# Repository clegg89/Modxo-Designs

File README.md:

# Modxo Designs
A set of custom [Modxo](https://github.com/Team-Resurgent/modxo) boards.

All boards have 128Mb (16MB) of flash and use a custom board variant.

## Comparison

| Feature | Micro | Mini | Mega |
| ------- | ----- | ---- | ---- |
| 128Mb (16MB) of flash | ✅ | ✅ | ✅ |
| On-board RGB LED | ✅ | ✅ | ✅ |
| USB port for DFU Update | ✅ | ✅ | ✅ |
| D0 Port/Solder Pad | ✅ | ✅ | ✅ |
| Xbox I2C Port | ❌ | ✅ | ✅ |
| LCD Support | ❌ | ✅ | ✅ |
| RGB Output Port | ❌ | ✅ | ✅ |
| Expansion I2C Port | ❌ | ✅ | ✅ |
| RP2350 MCU | ❌ | ❌ | ✅ |
| UART Port | ❌ | ❌ | ✅ |
| Micro SD Card Slot | ❌ | ❌ | ✅ |
| Debug Support | ❌ | ❌ | ✅ |
| R3MUX (X3) Support | ❌ | ❌ | ✅ |

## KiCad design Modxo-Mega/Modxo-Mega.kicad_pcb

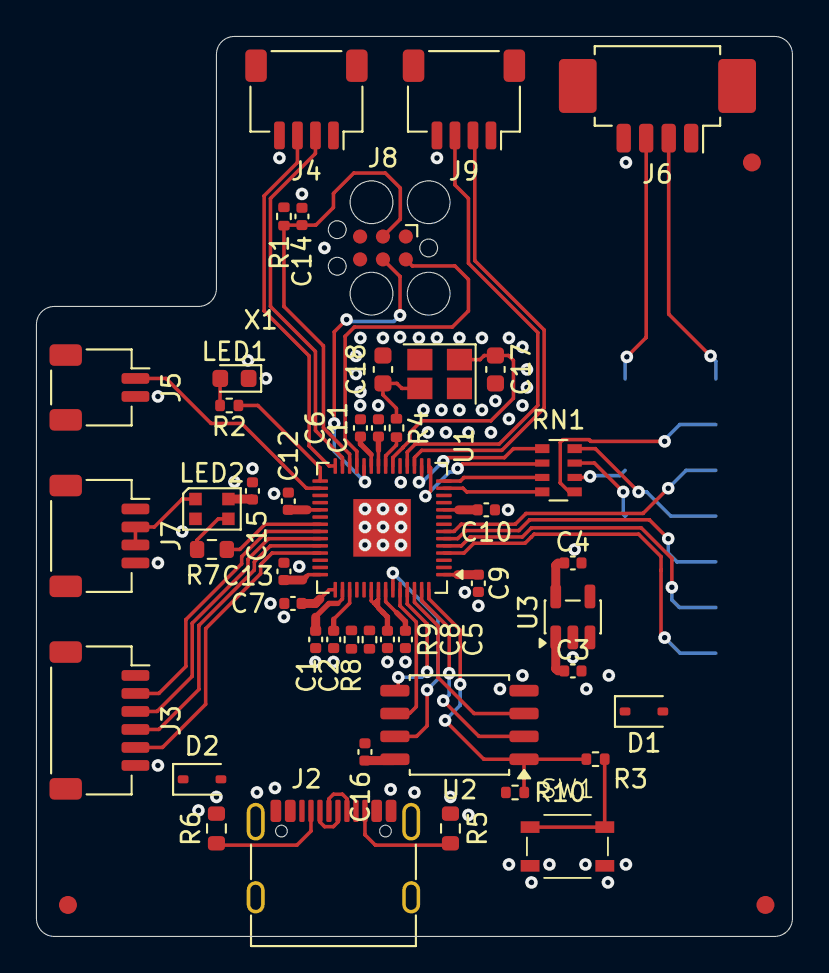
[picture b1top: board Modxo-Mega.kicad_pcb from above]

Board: 2 copper layers, 42.0 x 50.0 mm, 50 parts (1 on the bottom side), 53 nets.

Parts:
C1, C2, C3, C4: 1u; C_0402_1005Metric
C5, C6, C7, C8, C9, C10, C11, C12, C13, C14, C15, C16: 100n; C_0402_1005Metric
C17, C18: 15p; C_0603_1608Metric
D1, D2: 1N5819WS; D_SOD-323
FID1, FID2, FID3: Fiducial; Fiducial_1mm_Mask2mm
J1: LPC; PinSocket_2x08_P2.54mm_Vertical_SMD
J2: USB-C; USB_C_Receptacle_G-Switch_GT-USB-7010ASV
J3: LCD; JST_SH_SM06B-SRSS-TB_1x06-1MP_P1.00mm_Horizontal
J4: UART; JST_SH_SM04B-SRSS-TB_1x04-1MP_P1.00mm_Horizontal
J5: D0; JST_SH_SM02B-SRSS-TB_1x02-1MP_P1.00mm_Horizontal
J6: OXHD; Molex_PicoBlade_53261-0471_1x04-1MP_P1.25mm_Horizontal
J7: RGB; JST_SH_SM04B-SRSS-TB_1x04-1MP_P1.00mm_Horizontal
J8: DBG; Tag-Connect_TC2030-IDC-FP_2x03_P1.27mm_Vertical
J9: EXP I2C; JST_SH_SM04B-SRSS-TB_1x04-1MP_P1.00mm_Horizontal
LED1: LED; LED_0603_1608Metric
LED2: WS2812B-2020; LED_WS2812B-2020_PLCC4_2.0x2.0mm
R1, R2, R3, R4: 1k; R_0402_1005Metric
R5, R6: 5k1; R_0603_1608Metric
R7: 470; R_0603_1608Metric
R8, R9: 27; R_0402_1005Metric
R10: DNP; R_0402_1005Metric
RN1: 100; R_Array_Convex_4x0603
SW1: Boot; SW_SPST_TS34425BA
U1: RP2040; QFN-56-1EP_7x7mm_P0.4mm_EP3.2x3.2mm
U2: W25Q128JVS; SOIC-8_5.3x5.3mm_P1.27mm
U3: AP2112K-3.3; SOT-23-5
X1: 12MHz; Crystal_SMD_Abracon_ABM8AIG-4Pin_3.2x2.5mm

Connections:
+1V1: C2.1, C5.1, C6.1, U1.23 (DVDD), U1.45 (VREG_VOUT), U1.50 (DVDD)
+3V3: C1.1, C4.1, C7.1, C8.1, C9.1, C10.1, C11.1, C12.1, C13.1, C16.1, J8.1 (VCC), R1.1, R10.1, U1.1 (IOVDD), U1.10 (IOVDD), U1.22 (IOVDD), U1.33 (IOVDD), U1.42 (IOVDD), U1.43 (ADC_AVDD), U1.44 (VREG_VIN), U1.48 (USB_VDD), U1.49 (IOVDD), U2.8 (VCC), U3.5 (VOUT)
+VBUS: D2.2 (A), J2.A4 (VBUS), J2.A9 (VBUS), J2.B4 (VBUS), J2.B9 (VBUS)
+VSYS: C3.1, C15.1, D1.1 (K), D2.1 (K), J3.1, J4.1, J6.1, J7.1, J9.1, LED2.4 (VDD), U3.1 (VIN), U3.3 (EN)
/+LPC_5V: D1.2 (A), J1.6
/D0: J5.1, U1.30 (GPIO19)
/DBG_NRST: C14.1, J8.3 (~RESET), R1.2, U1.26 (RUN)
/DBG_SWCLK: J8.4 (SWCLK), U1.24 (SWCLK)
/DBG_SWDIO: J8.2 (SWDIO), U1.25 (SWDIO)
/EXP_SCL: J9.3, U1.18 (GPIO15)
/EXP_SDA: J9.2, U1.17 (GPIO14)
/LAD0: J1.11, RN1.5 (R4.2)
/LAD0R: RN1.4 (R4.1), U1.13 (GPIO10)
/LAD1: J1.10, RN1.6 (R3.2)
/LAD1R: RN1.3 (R3.1), U1.14 (GPIO11)
/LAD2: J1.8, RN1.7 (R2.2)
/LAD2R: RN1.2 (R2.1), U1.15 (GPIO12)
/LAD3: J1.7, RN1.8 (R1.2)
/LAD3R: RN1.1 (R1.1), U1.16 (GPIO13)
/LCD_CSN1: J3.2, U1.36 (GPIO24)
/LCD_CSN2: J3.3, U1.37 (GPIO25)
/LCD_SPI_SCK: J3.4, U1.38 (GPIO26/ADC0)
/LCD_SPI_TX: J3.5, U1.39 (GPIO27/ADC1)
/LED: LED1.2 (A), R2.2
/LEDR: R2.1, U1.29 (GPIO18)
/LPC_3V3: J1.9, U1.7 (GPIO5)
/LPC_LCLK: J1.1, U1.4 (GPIO2)
/LPC_LFRAME: J1.3, U1.5 (GPIO3)
/LPC_RST: J1.5, U1.6 (GPIO4)
/QSPI_SCLK: U1.52 (QSPI_SCLK), U2.6 (CLK)
/QSPI_SD0: U1.53 (QSPI_SD0), U2.5 (DI/IO_{0})
/QSPI_SD1: U1.55 (QSPI_SD1), U2.2 (DO/IO_{1})
/QSPI_SD2: U1.54 (QSPI_SD2), U2.3 (~WP/IO_{2})
/QSPI_SD3: U1.51 (QSPI_SD3), U2.7 (~HOLD/~RESET/IO_{3})
/QSPI_SS: R3.2, R10.2, U1.56 (~QSPI_SS), U2.1 (~CS)
/RGB_DIN: LED2.3 (DIN), R7.2
/RGB_DINR: R7.1, U1.35 (GPIO23)
/RGB_DOUT: J7.2, J7.3, LED2.1 (DOUT)
/UART_RX: J4.3, U1.28 (GPIO17)
/UART_TX: J4.2, U1.27 (GPIO16)
/USBCC1: J2.A5 (CC1), R6.1
/USBCC2: J2.B5 (CC2), R5.1
/USBD+: J2.A6 (D+), J2.B6 (D+), R9.2
/USBD-: J2.A7 (D-), J2.B7 (D-), R8.2
/USB_BOOT: R3.1, SW1.1
/USB_DM-: R8.1, U1.46 (USB_DM)
/USB_DP+: R9.1, U1.47 (USB_DP)
/XIN: C17.1, U1.20 (XIN), X1.1
/XOUT: R4.1, U1.21 (XOUT)
/XOUTC: C18.2, R4.2, X1.3
/XSMBUS_SCL: J1.13, J6.2
/XSMBUS_SDA: J1.14, J6.3
GND: C1.2, C2.2, C3.2, C4.2, C5.2, C6.2, C7.2, C8.2, C9.2, C10.2, C11.2, C12.2, C13.2, C14.2, C15.2, C16.2, C17.2, C18.1, J1.2, J1.12, J2.A1 (GND), J2.A12 (GND), J2.B1 (GND), J2.B12 (GND), J2.SH (SHIELD), J3.6, J3.MP (MountPin), J4.4, J4.MP (MountPin), J5.2, J5.MP (MountPin), J6.4, J6.MP (MountPin), J7.4, J7.MP (MountPin), J8.5 (GND), J9.4, J9.MP (MountPin), LED1.1 (K), LED2.2 (VSS), R5.2, R6.2, SW1.2, U1.19 (TESTEN), U1.57 (GND), U2.4 (GND), U3.2 (GND), X1.2 (G), X1.4 (G)
